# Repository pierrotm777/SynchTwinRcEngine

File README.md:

# SynchTwinRcEngine
Synchronizer for two glow motors

Use an Arduino Uno or Pro Mini or Micro for command two glow RC motors.
The Arduino read the Radio Rc  throttle and command the two motors in same time .
The speed rotation is read by two sensors

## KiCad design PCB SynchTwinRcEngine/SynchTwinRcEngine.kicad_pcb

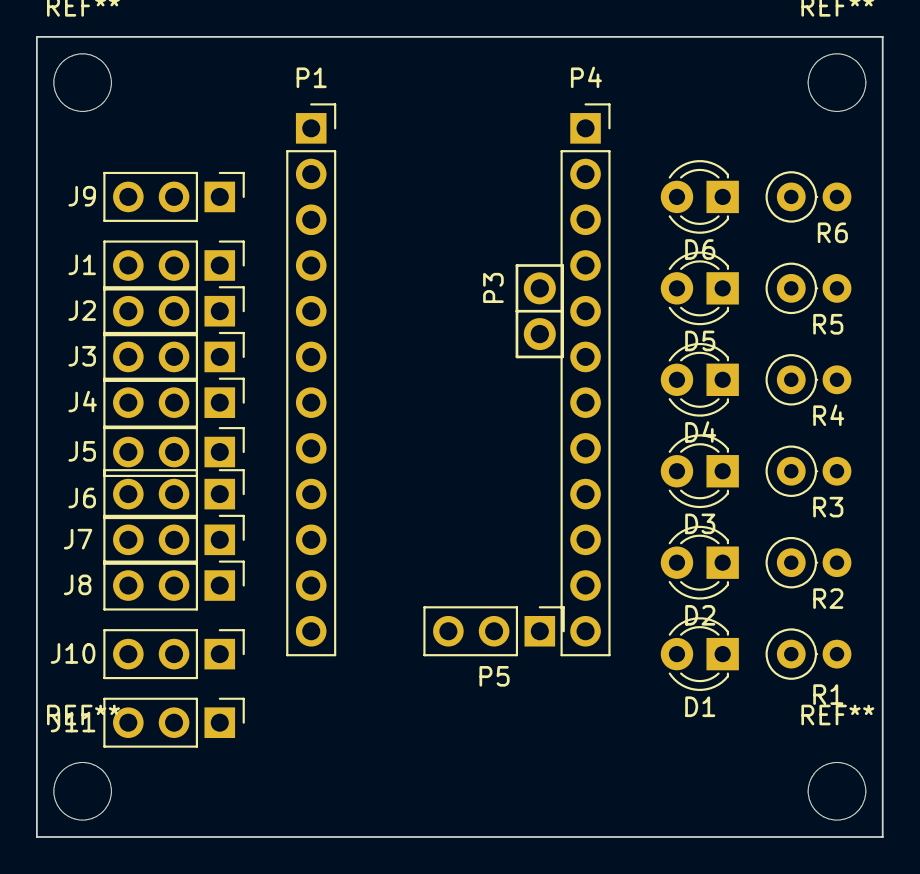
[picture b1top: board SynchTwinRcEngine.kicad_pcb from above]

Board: 2 copper layers, 47.0 x 44.4 mm, 27 parts (0 on the bottom side), 25 nets, no tracks yet.

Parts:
D1: RED1; LED_D3.0mm
D2: RED2; LED_D3.0mm
D3: GREEN1; LED_D3.0mm
D4: GREEN2; LED_D3.0mm
D5: YELLOW1; LED_D3.0mm
D6: YELLOW2; LED_D3.0mm
J1: Rx Output; PinHeader_1x03_P2.54mm_Vertical
J2: Sensor1; PinHeader_1x03_P2.54mm_Vertical
J3: Sensor2; PinHeader_1x03_P2.54mm_Vertical
J4: Servo1; PinHeader_1x03_P2.54mm_Vertical
J5: Servo2; PinHeader_1x03_P2.54mm_Vertical
J6: Servo3; PinHeader_1x03_P2.54mm_Vertical
J7: Glow1; PinHeader_1x03_P2.54mm_Vertical
J8: Glow2; PinHeader_1x03_P2.54mm_Vertical
J9: RPM Outputs; PinHeader_1x03_P2.54mm_Vertical
J10: Settings; PinHeader_1x03_P2.54mm_Vertical
J11: External Vbat; PinHeader_1x03_P2.54mm_Vertical
P1: Digital; PinSocket_1x12_P2.54mm_Vertical
P3: ADC; Socket_Strip_Arduino_1x02
P4: Analog; PinSocket_1x12_P2.54mm_Vertical
P5: ADC; PinHeader_1x03_P2.54mm_Vertical
R1, R2, R3, R4, R5, R6: 220; R_Axial_DIN0207_L6.3mm_D2.5mm_P2.54mm_Vertical

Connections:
+5V: J1.2, J2.2, J3.2, J4.2, J5.2, J6.2, J7.2, J8.2, P4.4
/A0: D3.2, P4.8
/A1: D4.2, P4.7
/A2: D5.2, P4.6
/A3: D6.2, P4.5
/A7: J11.1, P5.1
/D0: J1.1, P1.2
/D1: J9.1, P1.1
/D2: J2.1, P1.5
/D3: J3.1, P1.6
/D4: J4.1, P1.7
/D5: J5.1, P1.8
/D6: J6.1, P1.9
/D7: J7.1, P1.10
/D8: J8.1, P1.11
/D9: J9.3, P1.12
/D10: D1.2, J10.2, P4.12
/D11: D2.2, J10.1, P4.11
GND: J1.3, J2.3, J3.3, J4.3, J5.3, J6.3, J7.3, J8.3, J9.2, J10.3, J11.2, P1.4, P4.3, P5.3, R1.2, R2.2, R3.2, R4.2, R5.2, R6.2
unnamed: D1.1, R1.1
unnamed: D2.1, R2.1
unnamed: D3.1, R3.1
unnamed: D4.1, R4.1
unnamed: D5.1, R5.1
unnamed: D6.1, R6.1

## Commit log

2017-09-09 Ajout sources arduino
2017-09-09 Ajout sources interface VB.net 2010
    Interface de programmation du module SynchTwinRcEngine (VB.NET 2010)
2020-03-17 Remove all files
2020-03-17 Add My last version
    -Add Arduino code
    -Add VB.NET 2010 code (interface)
2020-03-29 Replace PWM input by CPPM input
2020-03-29 Add Recoder and Glow control
2020-03-29 Put main variables in a structure
2020-03-29 Add SBUS and IBUS input modes
2020-03-30 Add rudder ouput
2020-04-26 Update
    Add Radio Modes 1 to 4
    Add Signal Input CPPM, SBUS and IBUS
2020-04-27 Check PPM input OK
2020-04-28 Change Serial port for settings
2020-04-28 Create version 3_4
2020-05-17 Add V4 version
    - Add chech VB connection
    - Add servo recorder
    - Protocols usable are PPM,SBUS,SRXL,SUMD,IBUS and JETI
2020-05-22 Save settings issue solved
2020-05-22 Add On Off Glowplug and Simu On Off
2020-05-23 remove V3 versions
2020-06-01 Update VB é Arduino codes
    -Remove RcMode
    -Add Channels Order
2020-06-02 Update Glow drivers & LED uses
2020-06-04 Uptade External Battery Voltage code
    - Update debug code
    - Add voltage coeff to eeprom structure in VB & C++
2020-06-04 remove frsky telemetry code
2020-06-06 Add output pins for RPM telemetry
    Set pins D1 and D9 as output pin for telemetry
2020-06-09 Update RcRadioMode form
2020-06-12 Add Kicad files (schematic & PCB)
2020-06-14 Update
    -Read sensors issue solved
    -Red led not stop serial port
2020-06-14 Update RPM output code
2020-06-15 Update
    Debug simulation servo moving
2020-06-19 Add Channel Auxiliary Number
2020-06-21 Check Internal & External voltages in VB settings
2020-07-22 Add OpenLog feature
